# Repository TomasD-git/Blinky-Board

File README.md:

# Blinky-Board
## Blinky board with 10 LEDS
----

## Schematic
**uses 2 ics, 1 is a timer that times so 2 dont light up at the same time and other to actually power them, it has 270ohm resistor which is best for red LEDs**

## PCB
**Made it heart shaped with cool art, spaced out components and my name at the back**

### 3D viewer

----
### Bom includes the kit from stasis and the pcb on which are all the components

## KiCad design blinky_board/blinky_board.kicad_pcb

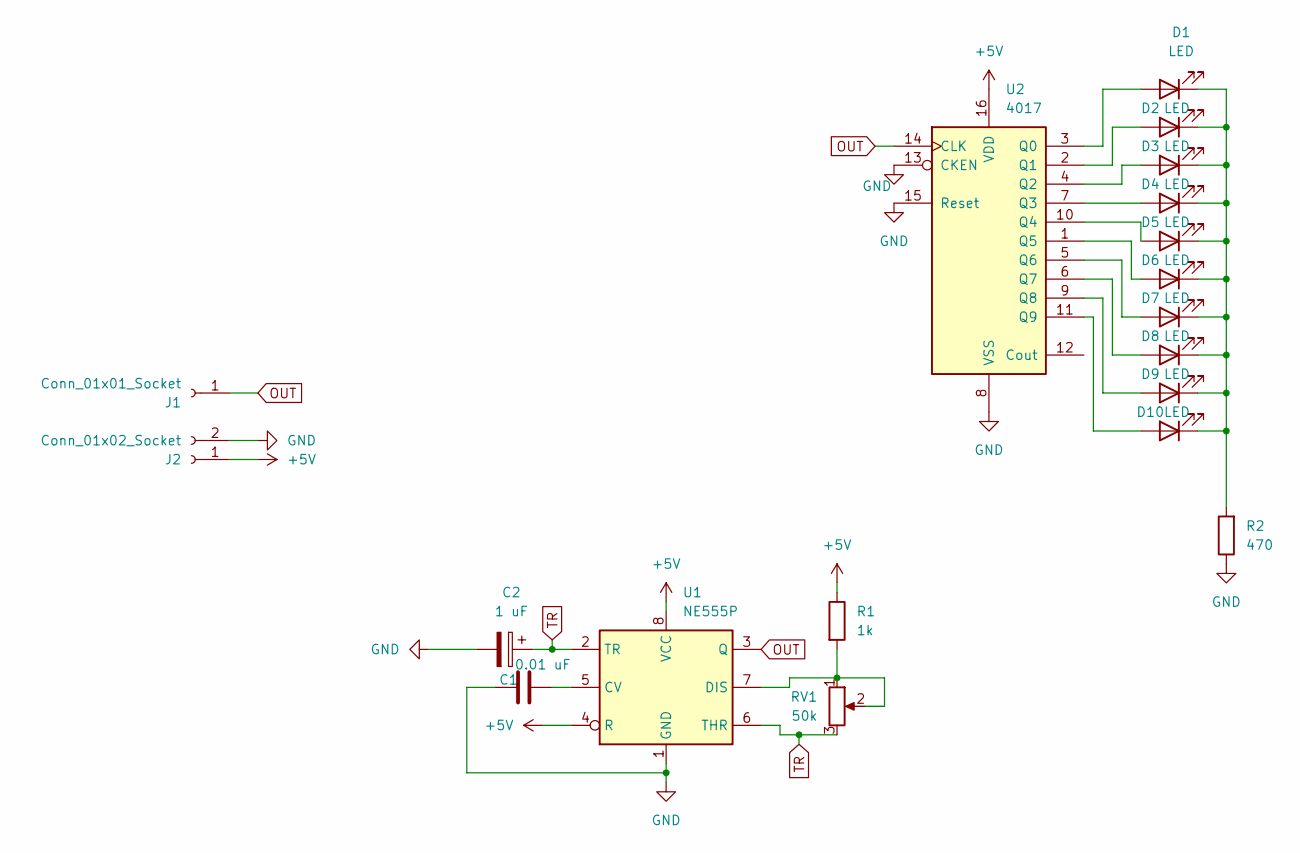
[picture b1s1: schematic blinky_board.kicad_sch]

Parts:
C1: 0.01 uF; C_Disc_D7.5mm_W2.5mm_P5.00mm
C2: 1 uF; CP_Radial_D5.0mm_P2.00mm
D1, D2, D3, D4, D5, D6, D7, D8, D9, D10: LED; LED_D3.0mm
J1: Conn_01x01_Socket; PinHeader_1x01_P2.54mm_Vertical
J2: Conn_01x02_Socket; PinHeader_1x02_P2.54mm_Vertical
R1: 1k; R_Axial_DIN0207_L6.3mm_D2.5mm_P7.62mm_Horizontal
R2: 470; R_Axial_DIN0207_L6.3mm_D2.5mm_P7.62mm_Horizontal
RV1: 50k; Potentiometer_Vishay_T93YA_Vertical
U1: NE555P; DIP-8_W7.62mm
U2: 4017; N16

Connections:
+5V: J2.1, R1.1, U1.4 (R), U1.8 (VCC), U2.16 (VDD)
GND: C1.1, C2.2, J2.2, R2.1, U1.1 (GND), U2.8 (VSS), U2.13 (CKEN), U2.15 (Reset)
unnamed: D1.2 (A), U2.3 (Q0)
unnamed: D1.1 (K), D2.1 (K), D3.1 (K), D4.1 (K), D5.1 (K), D6.1 (K), D7.1 (K), D8.1 (K), D9.1 (K), D10.1 (K), R2.2
unnamed: D2.2 (A), U2.2 (Q1)
unnamed: D3.2 (A), U2.4 (Q2)
unnamed: D4.2 (A), U2.7 (Q3)
unnamed: D5.2 (A), U2.10 (Q4)
unnamed: D6.2 (A), U2.1 (Q5)
unnamed: D7.2 (A), U2.5 (Q6)
unnamed: D8.2 (A), U2.6 (Q7)
unnamed: D9.2 (A), U2.9 (Q8)
unnamed: D10.2 (A), U2.11 (Q9)
unnamed: C1.2, U1.5 (CV)
unnamed: R1.2, RV1.1, RV1.2, U1.7 (DIS)
OUT: J1.1, U1.3 (Q), U2.14 (CLK)
TR: C2.1, RV1.3, U1.2 (TR), U1.6 (THR)

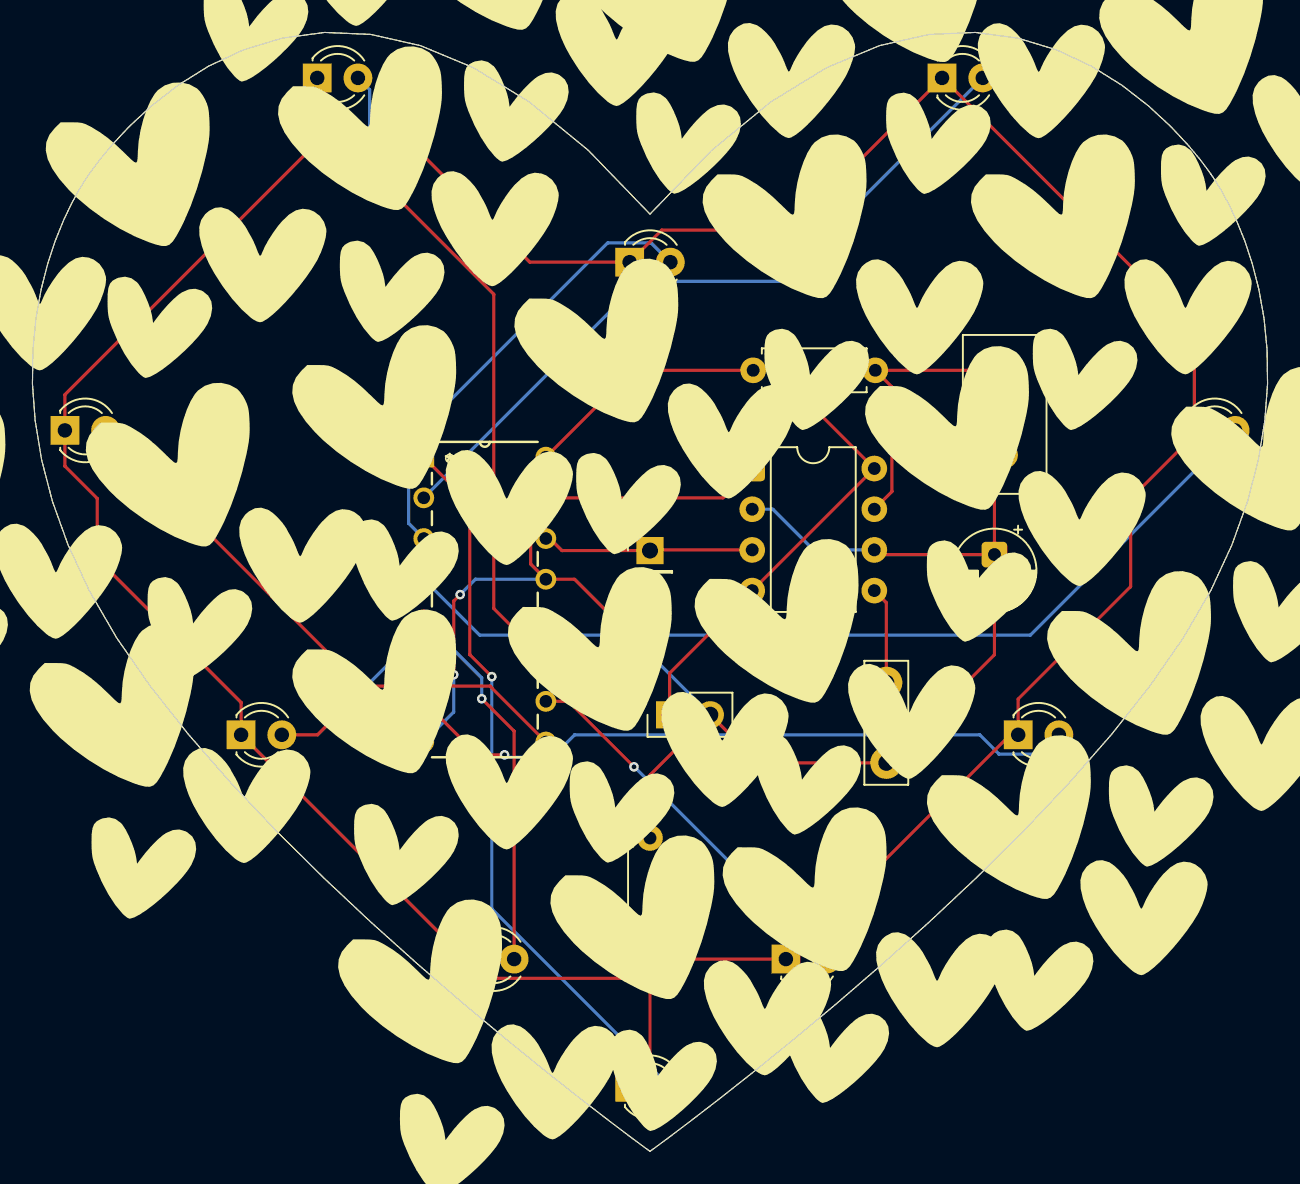
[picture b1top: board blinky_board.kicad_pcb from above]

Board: 2 copper layers, 77.1 x 69.8 mm, 19 parts (0 on the bottom side), 17 nets.

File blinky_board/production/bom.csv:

Designator,Footprint,Quantity,Value,LCSC Part #
C1,C_Disc_D7.5mm_W2.5mm_P5.00mm,1,0.01 uF,
C2,CP_Radial_D5.0mm_P2.00mm,1,1 uF,
"D1, D10, D2, D3, D4, D5, D6, D7, D8, D9",LED_D3.0mm,10,LED,
J1,PinHeader_1x01_P2.54mm_Vertical,1,Conn_01x01_Socket,
J2,PinHeader_1x02_P2.54mm_Vertical,1,Conn_01x02_Socket,
R1,R_Axial_DIN0207_L6.3mm_D2.5mm_P7.62mm_Horizontal,1,1k,
R2,R_Axial_DIN0207_L6.3mm_D2.5mm_P7.62mm_Horizontal,1,470,
RV1,Potentiometer_Vishay_T93YA_Vertical,1,50k,
U1,DIP-8_W7.62mm,1,NE555P,
U2,N16,1,4017,

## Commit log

2026-05-03 added kicad files
2026-05-03 added PCB
2026-05-03 Enhance README with additional project details
    Added schematic, PCB details, and 3D viewer images to README.
2026-05-03 added BOM
